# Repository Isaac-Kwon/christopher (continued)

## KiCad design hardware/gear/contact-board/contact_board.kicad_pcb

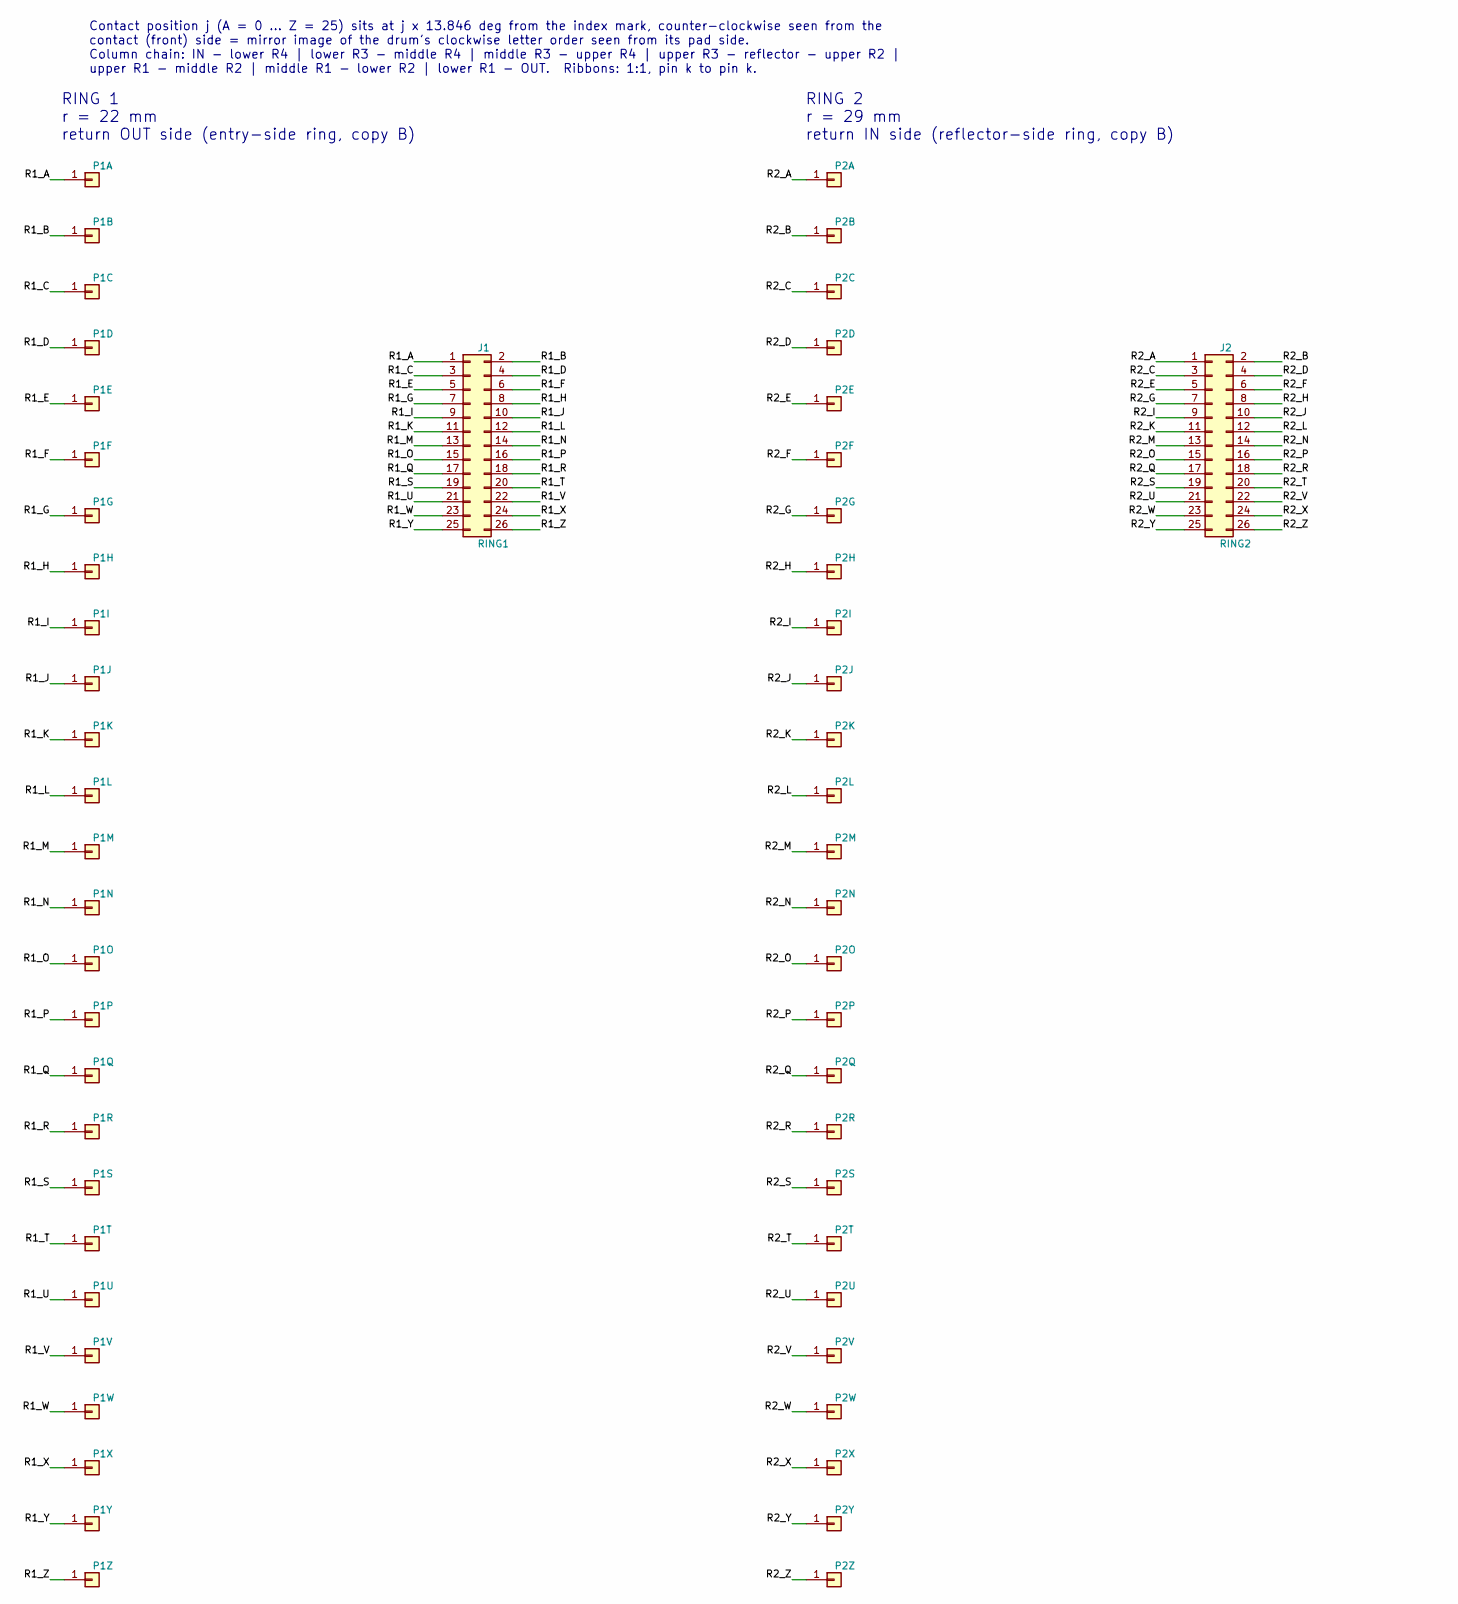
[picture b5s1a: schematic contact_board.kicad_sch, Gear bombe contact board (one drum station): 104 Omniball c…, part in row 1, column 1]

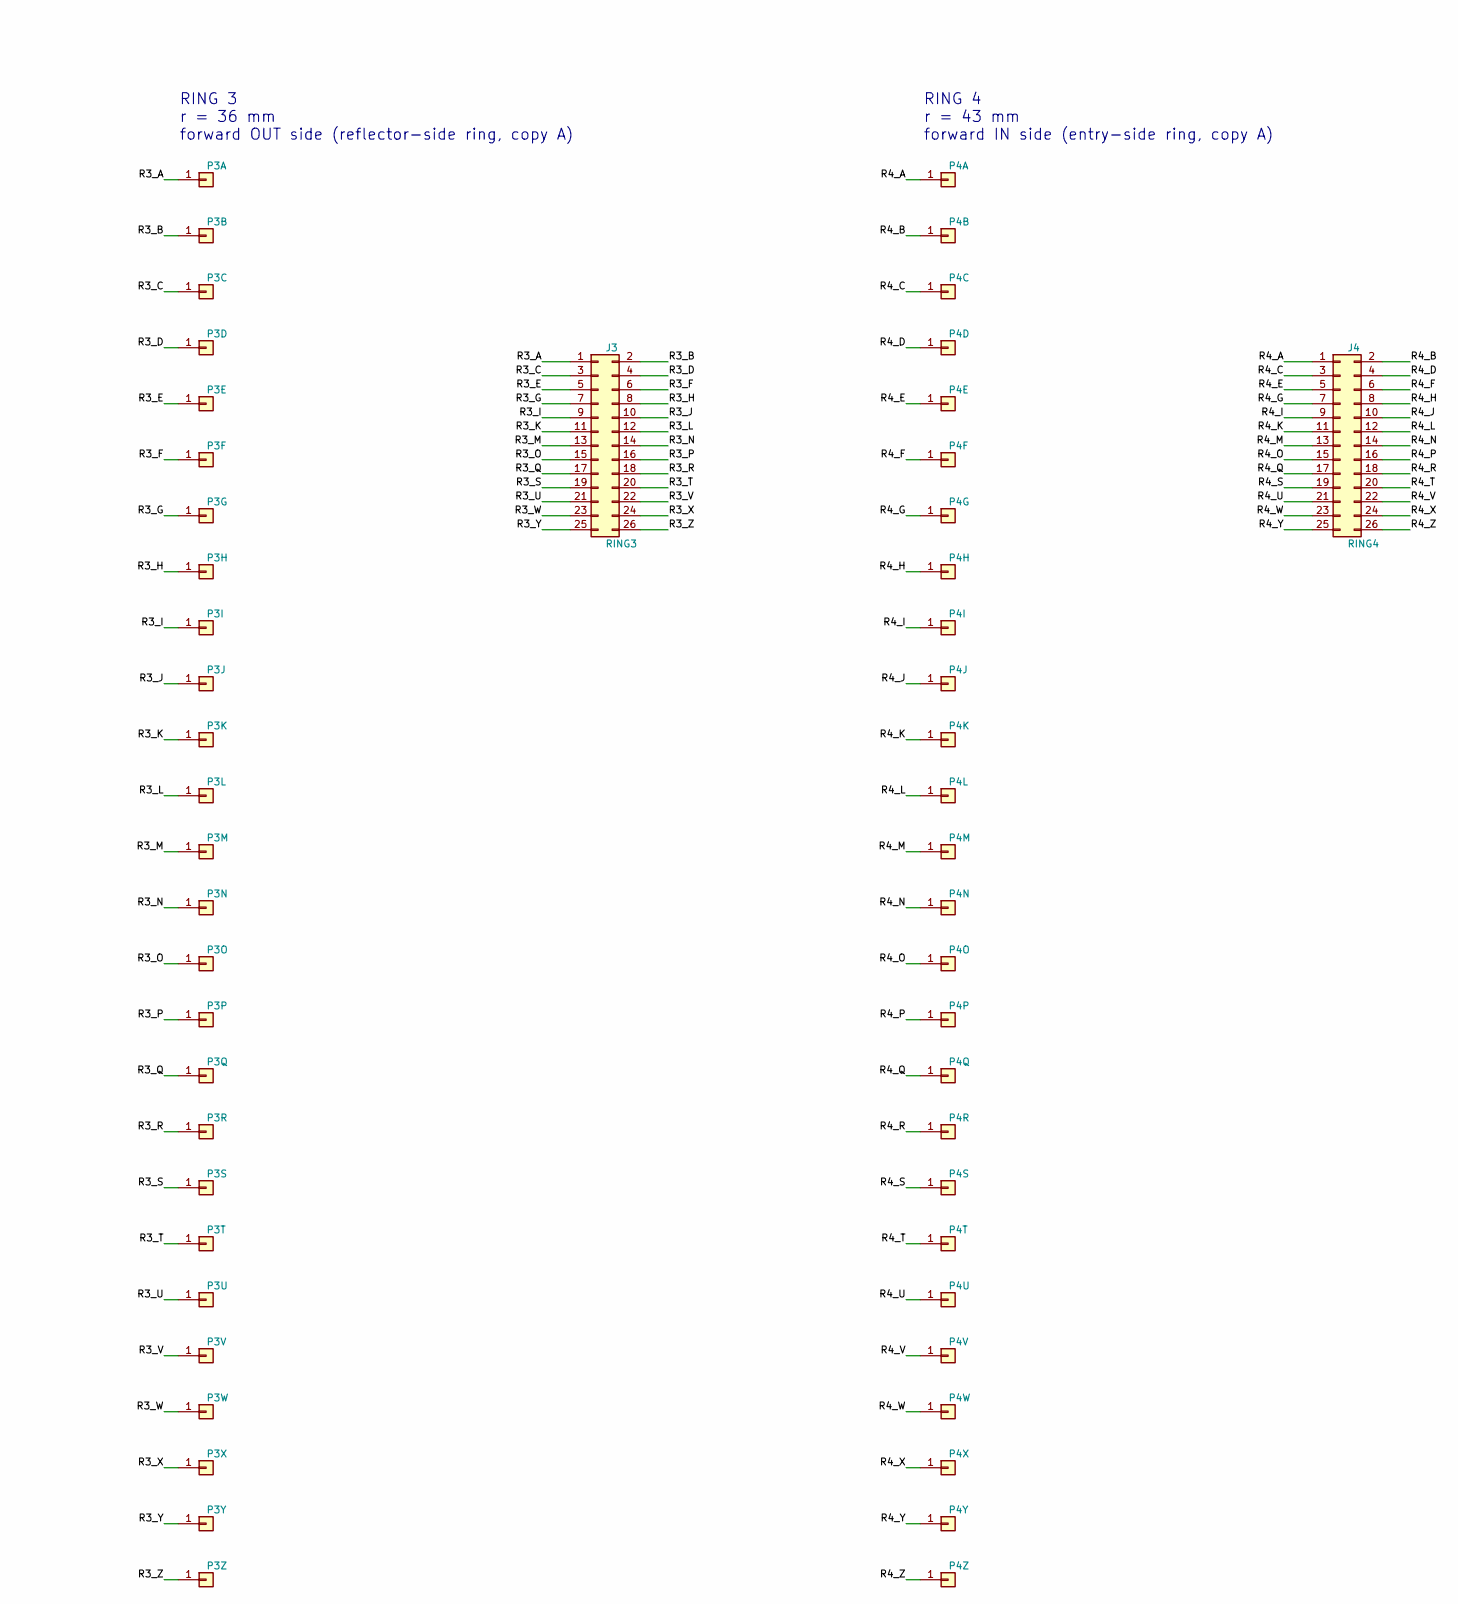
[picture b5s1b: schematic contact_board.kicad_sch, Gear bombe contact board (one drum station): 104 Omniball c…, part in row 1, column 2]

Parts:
J1: RING1; IDC-Header_2x13_P2.54mm_Vertical
J2: RING2; IDC-Header_2x13_P2.54mm_Vertical
J3: RING3; IDC-Header_2x13_P2.54mm_Vertical
J4: RING4; IDC-Header_2x13_P2.54mm_Vertical
P1A: 7845-0 R1A; Omniball_7845-0-15-20-52-14-11-0
P1B: 7845-0 R1B; Omniball_7845-0-15-20-52-14-11-0
P1C: 7845-0 R1C; Omniball_7845-0-15-20-52-14-11-0
P1D: 7845-0 R1D; Omniball_7845-0-15-20-52-14-11-0
P1E: 7845-0 R1E; Omniball_7845-0-15-20-52-14-11-0
P1F: 7845-0 R1F; Omniball_7845-0-15-20-52-14-11-0
P1G: 7845-0 R1G; Omniball_7845-0-15-20-52-14-11-0
P1H: 7845-0 R1H; Omniball_7845-0-15-20-52-14-11-0
P1I: 7845-0 R1I; Omniball_7845-0-15-20-52-14-11-0
P1J: 7845-0 R1J; Omniball_7845-0-15-20-52-14-11-0
P1K: 7845-0 R1K; Omniball_7845-0-15-20-52-14-11-0
P1L: 7845-0 R1L; Omniball_7845-0-15-20-52-14-11-0
P1M: 7845-0 R1M; Omniball_7845-0-15-20-52-14-11-0
P1N: 7845-0 R1N; Omniball_7845-0-15-20-52-14-11-0
P1O: 7845-0 R1O; Omniball_7845-0-15-20-52-14-11-0
P1P: 7845-0 R1P; Omniball_7845-0-15-20-52-14-11-0
P1Q: 7845-0 R1Q; Omniball_7845-0-15-20-52-14-11-0
P1R: 7845-0 R1R; Omniball_7845-0-15-20-52-14-11-0
P1S: 7845-0 R1S; Omniball_7845-0-15-20-52-14-11-0
P1T: 7845-0 R1T; Omniball_7845-0-15-20-52-14-11-0
P1U: 7845-0 R1U; Omniball_7845-0-15-20-52-14-11-0
P1V: 7845-0 R1V; Omniball_7845-0-15-20-52-14-11-0
P1W: 7845-0 R1W; Omniball_7845-0-15-20-52-14-11-0
P1X: 7845-0 R1X; Omniball_7845-0-15-20-52-14-11-0
P1Y: 7845-0 R1Y; Omniball_7845-0-15-20-52-14-11-0
P1Z: 7845-0 R1Z; Omniball_7845-0-15-20-52-14-11-0
P2A: 7845-0 R2A; Omniball_7845-0-15-20-52-14-11-0
P2B: 7845-0 R2B; Omniball_7845-0-15-20-52-14-11-0
P2C: 7845-0 R2C; Omniball_7845-0-15-20-52-14-11-0
P2D: 7845-0 R2D; Omniball_7845-0-15-20-52-14-11-0
P2E: 7845-0 R2E; Omniball_7845-0-15-20-52-14-11-0
P2F: 7845-0 R2F; Omniball_7845-0-15-20-52-14-11-0
P2G: 7845-0 R2G; Omniball_7845-0-15-20-52-14-11-0
P2H: 7845-0 R2H; Omniball_7845-0-15-20-52-14-11-0
P2I: 7845-0 R2I; Omniball_7845-0-15-20-52-14-11-0
P2J: 7845-0 R2J; Omniball_7845-0-15-20-52-14-11-0
P2K: 7845-0 R2K; Omniball_7845-0-15-20-52-14-11-0
P2L: 7845-0 R2L; Omniball_7845-0-15-20-52-14-11-0
P2M: 7845-0 R2M; Omniball_7845-0-15-20-52-14-11-0
P2N: 7845-0 R2N; Omniball_7845-0-15-20-52-14-11-0
P2O: 7845-0 R2O; Omniball_7845-0-15-20-52-14-11-0
P2P: 7845-0 R2P; Omniball_7845-0-15-20-52-14-11-0
P2Q: 7845-0 R2Q; Omniball_7845-0-15-20-52-14-11-0
P2R: 7845-0 R2R; Omniball_7845-0-15-20-52-14-11-0
P2S: 7845-0 R2S; Omniball_7845-0-15-20-52-14-11-0
P2T: 7845-0 R2T; Omniball_7845-0-15-20-52-14-11-0
P2U: 7845-0 R2U; Omniball_7845-0-15-20-52-14-11-0
P2V: 7845-0 R2V; Omniball_7845-0-15-20-52-14-11-0
P2W: 7845-0 R2W; Omniball_7845-0-15-20-52-14-11-0
P2X: 7845-0 R2X; Omniball_7845-0-15-20-52-14-11-0
P2Y: 7845-0 R2Y; Omniball_7845-0-15-20-52-14-11-0
P2Z: 7845-0 R2Z; Omniball_7845-0-15-20-52-14-11-0
P3A: 7845-0 R3A; Omniball_7845-0-15-20-52-14-11-0
P3B: 7845-0 R3B; Omniball_7845-0-15-20-52-14-11-0
P3C: 7845-0 R3C; Omniball_7845-0-15-20-52-14-11-0
P3D: 7845-0 R3D; Omniball_7845-0-15-20-52-14-11-0
P3E: 7845-0 R3E; Omniball_7845-0-15-20-52-14-11-0
P3F: 7845-0 R3F; Omniball_7845-0-15-20-52-14-11-0
P3G: 7845-0 R3G; Omniball_7845-0-15-20-52-14-11-0
P3H: 7845-0 R3H; Omniball_7845-0-15-20-52-14-11-0
P3I: 7845-0 R3I; Omniball_7845-0-15-20-52-14-11-0
P3J: 7845-0 R3J; Omniball_7845-0-15-20-52-14-11-0
P3K: 7845-0 R3K; Omniball_7845-0-15-20-52-14-11-0
P3L: 7845-0 R3L; Omniball_7845-0-15-20-52-14-11-0
P3M: 7845-0 R3M; Omniball_7845-0-15-20-52-14-11-0
P3N: 7845-0 R3N; Omniball_7845-0-15-20-52-14-11-0
P3O: 7845-0 R3O; Omniball_7845-0-15-20-52-14-11-0
P3P: 7845-0 R3P; Omniball_7845-0-15-20-52-14-11-0
P3Q: 7845-0 R3Q; Omniball_7845-0-15-20-52-14-11-0
P3R: 7845-0 R3R; Omniball_7845-0-15-20-52-14-11-0
P3S: 7845-0 R3S; Omniball_7845-0-15-20-52-14-11-0
P3T: 7845-0 R3T; Omniball_7845-0-15-20-52-14-11-0
P3U: 7845-0 R3U; Omniball_7845-0-15-20-52-14-11-0
P3V: 7845-0 R3V; Omniball_7845-0-15-20-52-14-11-0
P3W: 7845-0 R3W; Omniball_7845-0-15-20-52-14-11-0
P3X: 7845-0 R3X; Omniball_7845-0-15-20-52-14-11-0
P3Y: 7845-0 R3Y; Omniball_7845-0-15-20-52-14-11-0
P3Z: 7845-0 R3Z; Omniball_7845-0-15-20-52-14-11-0
P4A: 7845-0 R4A; Omniball_7845-0-15-20-52-14-11-0
P4B: 7845-0 R4B; Omniball_7845-0-15-20-52-14-11-0
P4C: 7845-0 R4C; Omniball_7845-0-15-20-52-14-11-0
P4D: 7845-0 R4D; Omniball_7845-0-15-20-52-14-11-0
P4E: 7845-0 R4E; Omniball_7845-0-15-20-52-14-11-0
P4F: 7845-0 R4F; Omniball_7845-0-15-20-52-14-11-0
P4G: 7845-0 R4G; Omniball_7845-0-15-20-52-14-11-0
P4H: 7845-0 R4H; Omniball_7845-0-15-20-52-14-11-0
P4I: 7845-0 R4I; Omniball_7845-0-15-20-52-14-11-0
P4J: 7845-0 R4J; Omniball_7845-0-15-20-52-14-11-0
P4K: 7845-0 R4K; Omniball_7845-0-15-20-52-14-11-0
P4L: 7845-0 R4L; Omniball_7845-0-15-20-52-14-11-0
P4M: 7845-0 R4M; Omniball_7845-0-15-20-52-14-11-0
P4N: 7845-0 R4N; Omniball_7845-0-15-20-52-14-11-0
P4O: 7845-0 R4O; Omniball_7845-0-15-20-52-14-11-0
P4P: 7845-0 R4P; Omniball_7845-0-15-20-52-14-11-0
P4Q: 7845-0 R4Q; Omniball_7845-0-15-20-52-14-11-0
P4R: 7845-0 R4R; Omniball_7845-0-15-20-52-14-11-0
P4S: 7845-0 R4S; Omniball_7845-0-15-20-52-14-11-0
P4T: 7845-0 R4T; Omniball_7845-0-15-20-52-14-11-0
P4U: 7845-0 R4U; Omniball_7845-0-15-20-52-14-11-0
P4V: 7845-0 R4V; Omniball_7845-0-15-20-52-14-11-0
P4W: 7845-0 R4W; Omniball_7845-0-15-20-52-14-11-0
P4X: 7845-0 R4X; Omniball_7845-0-15-20-52-14-11-0
P4Y: 7845-0 R4Y; Omniball_7845-0-15-20-52-14-11-0
P4Z: 7845-0 R4Z; Omniball_7845-0-15-20-52-14-11-0

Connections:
/R1_A: J1.1, P1A.1
/R1_B: J1.2, P1B.1
/R1_C: J1.3, P1C.1
/R1_D: J1.4, P1D.1
/R1_E: J1.5, P1E.1
/R1_F: J1.6, P1F.1
/R1_G: J1.7, P1G.1
/R1_H: J1.8, P1H.1
/R1_I: J1.9, P1I.1
/R1_J: J1.10, P1J.1
/R1_K: J1.11, P1K.1
/R1_L: J1.12, P1L.1
/R1_M: J1.13, P1M.1
/R1_N: J1.14, P1N.1
/R1_O: J1.15, P1O.1
/R1_P: J1.16, P1P.1
/R1_Q: J1.17, P1Q.1
/R1_R: J1.18, P1R.1
/R1_S: J1.19, P1S.1
/R1_T: J1.20, P1T.1
/R1_U: J1.21, P1U.1
/R1_V: J1.22, P1V.1
/R1_W: J1.23, P1W.1
/R1_X: J1.24, P1X.1
/R1_Y: J1.25, P1Y.1
/R1_Z: J1.26, P1Z.1
/R2_A: J2.1, P2A.1
/R2_B: J2.2, P2B.1
/R2_C: J2.3, P2C.1
/R2_D: J2.4, P2D.1
/R2_E: J2.5, P2E.1
/R2_F: J2.6, P2F.1
/R2_G: J2.7, P2G.1
/R2_H: J2.8, P2H.1
/R2_I: J2.9, P2I.1
/R2_J: J2.10, P2J.1
/R2_K: J2.11, P2K.1
/R2_L: J2.12, P2L.1
/R2_M: J2.13, P2M.1
/R2_N: J2.14, P2N.1
/R2_O: J2.15, P2O.1
/R2_P: J2.16, P2P.1
/R2_Q: J2.17, P2Q.1
/R2_R: J2.18, P2R.1
/R2_S: J2.19, P2S.1
/R2_T: J2.20, P2T.1
/R2_U: J2.21, P2U.1
/R2_V: J2.22, P2V.1
/R2_W: J2.23, P2W.1
/R2_X: J2.24, P2X.1
/R2_Y: J2.25, P2Y.1
/R2_Z: J2.26, P2Z.1
/R3_A: J3.1, P3A.1
/R3_B: J3.2, P3B.1
/R3_C: J3.3, P3C.1
/R3_D: J3.4, P3D.1
/R3_E: J3.5, P3E.1
/R3_F: J3.6, P3F.1
/R3_G: J3.7, P3G.1
/R3_H: J3.8, P3H.1
/R3_I: J3.9, P3I.1
/R3_J: J3.10, P3J.1
/R3_K: J3.11, P3K.1
/R3_L: J3.12, P3L.1
/R3_M: J3.13, P3M.1
/R3_N: J3.14, P3N.1
/R3_O: J3.15, P3O.1
/R3_P: J3.16, P3P.1
/R3_Q: J3.17, P3Q.1
/R3_R: J3.18, P3R.1
/R3_S: J3.19, P3S.1
/R3_T: J3.20, P3T.1
/R3_U: J3.21, P3U.1
/R3_V: J3.22, P3V.1
/R3_W: J3.23, P3W.1
/R3_X: J3.24, P3X.1
/R3_Y: J3.25, P3Y.1
/R3_Z: J3.26, P3Z.1
/R4_A: J4.1, P4A.1
/R4_B: J4.2, P4B.1
/R4_C: J4.3, P4C.1
/R4_D: J4.4, P4D.1
/R4_E: J4.5, P4E.1
/R4_F: J4.6, P4F.1
/R4_G: J4.7, P4G.1
/R4_H: J4.8, P4H.1
/R4_I: J4.9, P4I.1
/R4_J: J4.10, P4J.1
/R4_K: J4.11, P4K.1
/R4_L: J4.12, P4L.1
/R4_M: J4.13, P4M.1
/R4_N: J4.14, P4N.1
/R4_O: J4.15, P4O.1
/R4_P: J4.16, P4P.1
/R4_Q: J4.17, P4Q.1
/R4_R: J4.18, P4R.1
/R4_S: J4.19, P4S.1
/R4_T: J4.20, P4T.1
/R4_U: J4.21, P4U.1
/R4_V: J4.22, P4V.1
/R4_W: J4.23, P4W.1
/R4_X: J4.24, P4X.1
/R4_Y: J4.25, P4Y.1
/R4_Z: J4.26, P4Z.1

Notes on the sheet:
RING 1 r = 22 mm return OUT side (entry-side ring, copy B)
RING 2 r = 29 mm return IN side (reflector-side ring, copy B)
RING 3 r = 36 mm forward OUT side (reflector-side ring, copy A)
RING 4 r = 43 mm forward IN side (entry-side ring, copy A)
Contact position j (A = 0 ... Z = 25) sits at j x 13.846 deg from the index mark, counter-clockwise seen from the contact (front) side = mirror image of the drum's clockwise letter order seen from its pad side. Column chain: IN - lower R4 | lower R3 - middle R4 | middle R3 - upper R4 | upper R3 - r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

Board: 4 copper layers, 112 parts (4 on the bottom side), 104 nets, no tracks yet.

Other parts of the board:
H1, H4: NPTH 3.2; NPTH_3.2mm
H2, H3: NPTH 3; NPTH_3mm

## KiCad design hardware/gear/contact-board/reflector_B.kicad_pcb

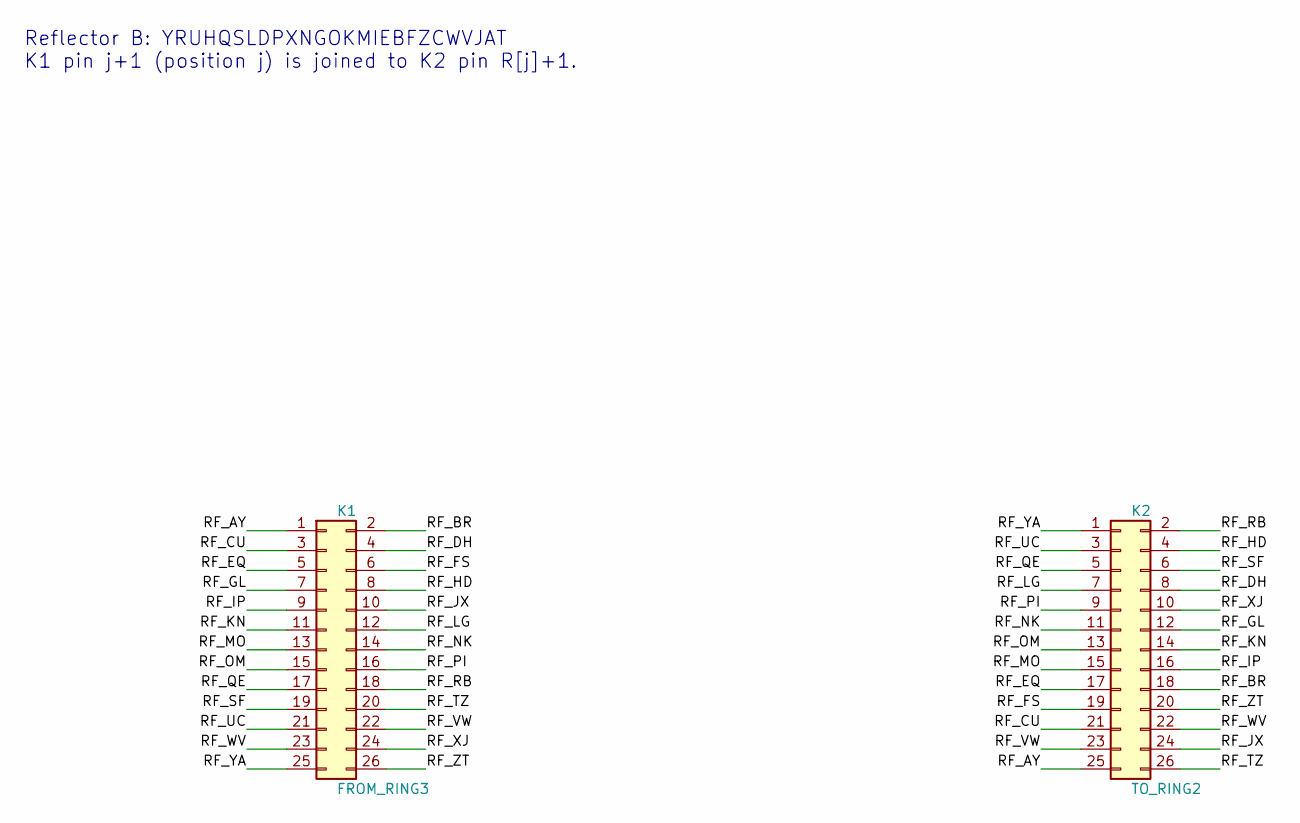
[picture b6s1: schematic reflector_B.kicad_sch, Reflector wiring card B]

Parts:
K1: FROM_RING3; IDC-Header_2x13_P2.54mm_Vertical
K2: TO_RING2; IDC-Header_2x13_P2.54mm_Vertical

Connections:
/RF_AY: K1.1, K2.25
/RF_BR: K1.2, K2.18
/RF_CU: K1.3, K2.21
/RF_DH: K1.4, K2.8
/RF_EQ: K1.5, K2.17
/RF_FS: K1.6, K2.19
/RF_GL: K1.7, K2.12
/RF_HD: K1.8, K2.4
/RF_IP: K1.9, K2.16
/RF_JX: K1.10, K2.24
/RF_KN: K1.11, K2.14
/RF_LG: K1.12, K2.7
/RF_MO: K1.13, K2.15
/RF_NK: K1.14, K2.11
/RF_OM: K1.15, K2.13
/RF_PI: K1.16, K2.9
/RF_QE: K1.17, K2.5
/RF_RB: K1.18, K2.2
/RF_SF: K1.19, K2.6
/RF_TZ: K1.20, K2.26
/RF_UC: K1.21, K2.3
/RF_VW: K1.22, K2.23
/RF_WV: K1.23, K2.22
/RF_XJ: K1.24, K2.10
/RF_YA: K1.25, K2.1
/RF_ZT: K1.26, K2.20

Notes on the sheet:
Reflector B: YRUHQSLDPXNGOKMIEBFZCWVJAT K1 pin j+1 (position j) is joined to K2 pin R[j]+1.

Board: 4 copper layers, 6 parts (2 on the bottom side), 26 nets, no tracks yet.

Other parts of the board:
H1, H2, H3, H4: NPTH 3.2; NPTH_3.2mm

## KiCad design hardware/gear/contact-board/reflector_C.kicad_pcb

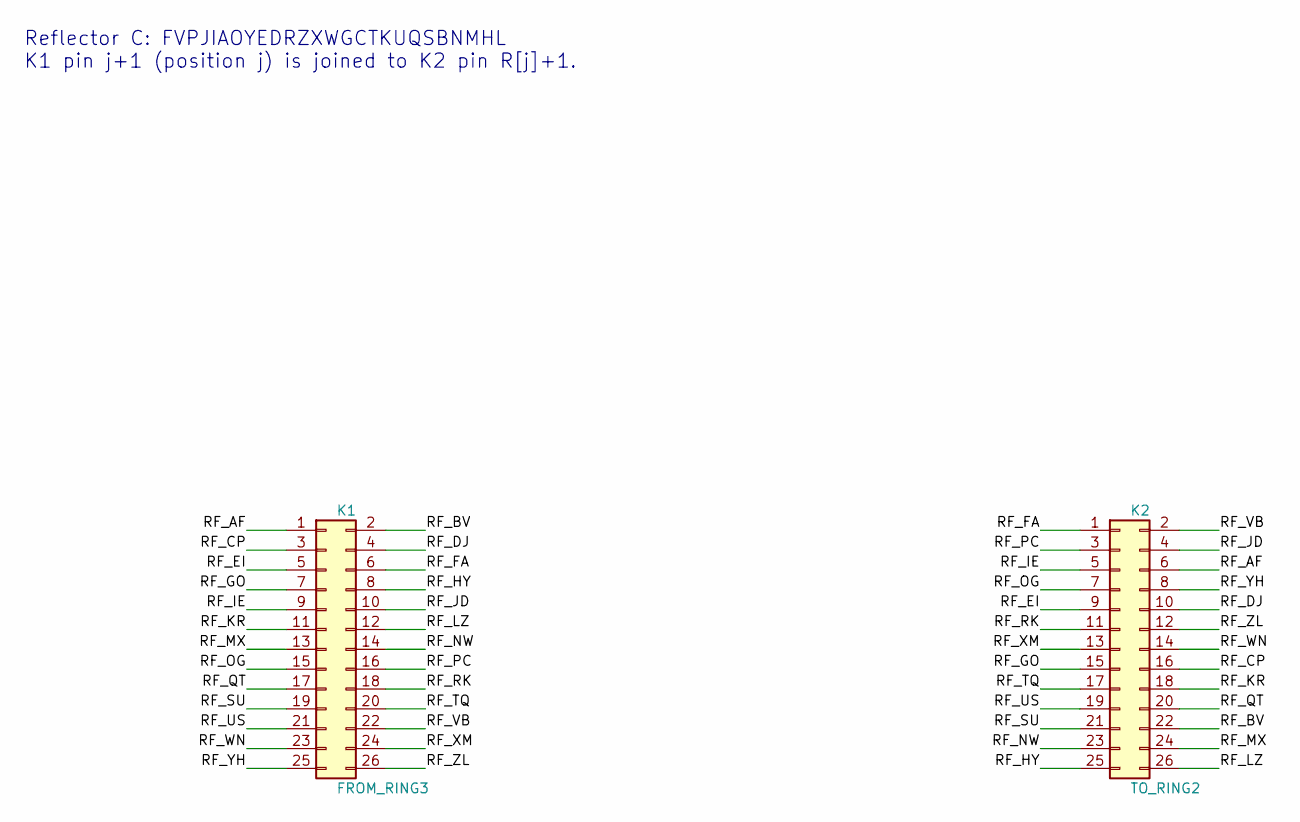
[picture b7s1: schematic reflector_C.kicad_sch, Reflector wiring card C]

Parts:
K1: FROM_RING3; IDC-Header_2x13_P2.54mm_Vertical
K2: TO_RING2; IDC-Header_2x13_P2.54mm_Vertical

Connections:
/RF_AF: K1.1, K2.6
/RF_BV: K1.2, K2.22
/RF_CP: K1.3, K2.16
/RF_DJ: K1.4, K2.10
/RF_EI: K1.5, K2.9
/RF_FA: K1.6, K2.1
/RF_GO: K1.7, K2.15
/RF_HY: K1.8, K2.25
/RF_IE: K1.9, K2.5
/RF_JD: K1.10, K2.4
/RF_KR: K1.11, K2.18
/RF_LZ: K1.12, K2.26
/RF_MX: K1.13, K2.24
/RF_NW: K1.14, K2.23
/RF_OG: K1.15, K2.7
/RF_PC: K1.16, K2.3
/RF_QT: K1.17, K2.20
/RF_RK: K1.18, K2.11
/RF_SU: K1.19, K2.21
/RF_TQ: K1.20, K2.17
/RF_US: K1.21, K2.19
/RF_VB: K1.22, K2.2
/RF_WN: K1.23, K2.14
/RF_XM: K1.24, K2.13
/RF_YH: K1.25, K2.8
/RF_ZL: K1.26, K2.12

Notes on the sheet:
Reflector C: FVPJIAOYEDRZXWGCTKUQSBNMHL K1 pin j+1 (position j) is joined to K2 pin R[j]+1.

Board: 4 copper layers, 6 parts (2 on the bottom side), 26 nets, no tracks yet.

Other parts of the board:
H1, H2, H3, H4: NPTH 3.2; NPTH_3.2mm

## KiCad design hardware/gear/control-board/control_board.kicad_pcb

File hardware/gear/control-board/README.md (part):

# 기어식 제어 보드 (구동부의 제어 보드, 회로도 · 시뮬레이션 · 기판 배치)

작성일: 2026-11-15 · 상태: **회로도(KiCad 10) 생성·ERC 0건, 넷리스트 구조 검사 335항목, 하드웨어·기구·펌웨어·릴레이 레지스터 연동 시뮬레이션, 음성 시험 19종, 기판 배치(미배선) 생성·검증 완료. 배선은 사용자가.** 같은 날 슬롯 원판의 각도(L4 여유)와 위치 원판의 모델(CAD와 일치)을 고치고, `HOME` 끝의 `CLEAR`(결정 0003 4.4절 (나))를 더함 · 관련: `docs/decisions/0003-interfaces.md`(4.2–4.6절, 5.2절, 6·7절), `docs/decisions/0001-test-register-timing.md`, `docs/decisions/0002-gear-detail-decisions.md` 5·10·11절, `hardware/gear/layout.md` 3.7·3.8절, `hardware/common/power-unit.md`, `hardware/common/unit-tester/README.md`(같은 부품 계열)

**표기.** **(계산)** = 이 문서의 산술, **(추정)** = 실측 전 값, **(미확인)** = 데이터시트로 확인하지 못한 것.

## 1. 무엇인가, 원칙

기어식 뱅크의 구동부에 들어가는 보드다. `docs/PLAN.md` 0절 7a의 미설계 항목이었다. 하는 일은 둘뿐이다.

1. **타이밍 신호 조건화**: 슬롯 원판의 광센서 셋 → `STROBE`·`JUDGE`·`CLEAR`를 24 V 레벨(결정 0003 2.2절)로 제어 커넥터에 낸다. 이 경로에는 **펌웨어가 없다**(센서 → RC → 74HC14 → 74HC 게이트 → TBD62783A → 자동 복귀 퓨즈 → 핀). 정지를 정하는 것은 테스트 레지스터의 릴레이다. 이 보드는 "언제"만 알린다.
2. **구동 제어**: 폐루프 스테퍼 구동기에 enable / step / dir를 주고(결정 0002 5절), 정지 자리로의 되돌림 · 재출발 · HOME · END · `POS` · 48 V 복귀 규칙을 맡는다. 마이크로컨트롤러는 **Raspberry Pi Pico**(단위 시험기와 같은 모듈)다. 전자 장치가 하는 일은 구동 제어와 신호 조건화에 한정되고 판정에는 관여하지 않는다(`design-brief.md` 1절).

구동기를 step / dir / enable로 고른 이유: 폐루프 스테퍼(예: Leadshine CS-M23485 계열)에는 자체 가감속 프로파일이 없다. 10,400 pps에서 정지 상태로부터 바로 스텝을 주면 탈조하므로 가감속 램프를 Pico가 만든다. "run / stop" 방식의 구동기는 속도 지령이 아날로그 또는 내부 프로그램이어서 되돌림(역회전, 위치 이동)을 못 한다. 구동기는 2,600 pulse/rev로 설정한다: 4:1 벨트에서 모터 한 바퀴 = 빠른 축 1/4 바퀴, 한 위치 = 13.846° (계산) = 모터 55.38° = **400 스텝**, 60 rpm = 26 위치/초 = **10,400 pps** (계산).

### 1.1 타이밍 경로 (하드웨어, 결정 0003 L1–L9)

```
광센서 3 (STROBE 트랙 · JUDGE 트랙 · CLEAR 트랙)
  → 4.7k 풀업(3.3 V) → 1k + 4.7n (약 5 µs) → 74HC14 → SLOT_S / SLOT_J / SLOT_C (하이 = 슬롯)
  STROBE_G = SLOT_S & TXE
  CLEAR_G  = SLOT_C & TXE
  JUDGE_G  = SLOT_J & SEEN & TXE
  TXE  = TXEN | CYC                      TXEN = Pico가 줌(HOME · 되돌림 중 0)
  CYC  : STROBE_G가 높은 동안 세트, CLEAR_G의 내림에서 클리어   (L7: 시작한 주기는 끝낸다)
         전원 투입 | HOMING에서 리셋 (74HC02의 남던 게이트: CYC_R_N = NOR(POR | HOMING))
  SEEN : STROBE_G의 오름에서 세트, 전원 투입 | HOMING | STOP_LATCH의 내림(RC 펄스)에서 클리어   (L8)
  → TBD62783A 채널(+24V_SW) → 자동 복귀 퓨즈(유지 30 mA 이상, 트립 100 mA 이하) → J_CTRL 핀 1 / 34 / 35
```

- 슬롯 각도(커넥터 면)는 `layout.md` 3.8절의 값이고, 원본은 CAD의 `hardware/gear/cad/params.py`(`SLOT_STEPS`, 한 위치 400스텝)다. 펌웨어 모델과 시뮬레이션이 그 파일을 읽는다: `STROBE` −26…+47스텝 = −2.50…+4.52 ms(보정 뒤 대표), `JUDGE` +89…+173 = +8.56…+16.63, `CLEAR` +194…+330 = +18.65…+31.73 (`STROBE` 접점 시작 기준, 패드 가운데는 +31.2스텝 = +3 ms, 60 rpm). 결정 0003 L2–L5에 각각 0.5 ms 이상의 공차 여유를 남긴 값이다(L2는 보정한 쪽의 식, 6절 1번). 보드는 **시간을 만들지 않는다**: 슬롯이 폭과 간격을 정한다. 폭 · 간격의 하한(L1–L6)은 속도가 60 rpm 이하이면 모든 구간이 시간으로 길어지므로 저속 · 가속 구간에서도 성립한다. 가감속 램프는 속도가 60 rpm을 넘지 않게 되어 있다.
- **L8을 STOP_LATCH의 내림 "에지"로** 지운다(레벨이 아님). 레벨로 하면 정지 판정(`JUDGE`) 도중 `STOP_LATCH`가 오를 때 `JUDGE`가 잘려 정지 릴레이가 자기 유지에 들기 전에 j가 열린다. 에지는 해제 때에만 지운다. 에지 펄스는 SL_N(= ¬STOP_LATCH)과 그 RC 지연(R61 47k · C51 10n, 약 0.5 ms)의 AND다.
- **CYC**가 필요한 이유: L7은 "`STROBE`를 낸 위치에는 `JUDGE`와 `CLEAR`를 반드시 낸다"이다. 펌웨어가 `TXEN`을 주기 한가운데서 내려도(되돌림) 시작한 주기는 끝난다.
- **CYC를 `HOMING`이 리셋하는 이유**(2026-11-15): `HOME`은 서 있을 때만 시작하고, 조작 정지와 정지 뒤 되돌림은 주기 사이에 서므로 그때 `CYC`는 이미 0이다. `CYC`가 남는 것은 비상 정지가 주기를 끊었을 때뿐이다(로직은 `+24V_L`이라 남는다). 그대로 두면 `+24V_SW`가 돌아올 때 슬롯 안에 서 있으면 그 출력이 나오고, `HOME`이 거꾸로 움직이면 그 칸의 `STROBE` 슬롯에서 `STROBE`가 나가며(0003 4.4 ① 위반), 앞으로 움직이면 `CLEAR`가 하나 더 나간다. 그래서 펌웨어는 비상 정지 때부터 `HOME`이 끝날 때까지 `HOMING`을 세워 두고(`SEEN`과 `CYC`를 지운 채), 끊긴 주기의 `CLEAR`는 `HOME` 끝의 `CLEAR`(1.2절)가 대신한다. 새 부품은 없다(74HC02의 남던 게이트 하나).
- **`HOME` 끝의 `CLEAR`**(결정 0003 4.4절 (나)): `CLEAR_G`는 `SEEN`을 보지 않으므로(`SLOT_C & TXE`), 펌웨어가 `HOMING`을 세운 채 `CLEAR` 슬롯 하나 동안만 `TXEN`을 올리면 `JUDGE` 없이 `CLEAR` 한 번이 나간다. 방법은 1.2절 표의 HOME.
- 슬롯 센서는 `+24V_SW`가 아니라 `+24V_L`에서 먹이고 출력단(TBD62783A U60)만 `+24V_SW`에서 먹인다(`power-unit.md` 2.2절). 비상 정지(`K_E`)가 `+24V_SW`를 끊으면 타이밍 출력과 PUL / DIR / ENA가 함께 사라진다.
- **보정**: STROBE 보정은 결정대로 센서 브래킷의 회전이며 이 보드에는 전자적 보정이 없다. 오실로스코프용으로 조건화한 슬롯 신호 `SLOT_S / SLOT_J / SLOT_C`와 0 V를 4핀 헤더 `J7`에 낸다(커넥터 면 신호는 `J_CTRL` 핀 1 / 34 / 35).

### 1.2 구동 제어 (펌웨어 모델 `firmware_model.py`)

실행 가능한 명세다(MicroPython으로 옮길 때의 기준). 상태: `REST · RUN · STOPDEC · CREEPOUT · RET · HBACK · HSEARCH · HDEC · HGO · HMOVE · HFLUSH`.

| 항목 | 동작 |
|---|---|
| 램프 | 가속 8×10⁵ steps/s², 정지 감속 1.2×10⁶ steps/s² (모터 축 약 1.1 / 1.3 N·m, 사다리꼴, **(추정)** G.2에서 확정). 속도는 10,400 pps를 넘지 않는다 |
| 48 V 복귀 규칙 (`power-unit.md` 4.2절) | `RUNARM`: `V48_OK`(KM3의 a 보조 접점, 24 V 레벨) 또는 `SW_OK`가 꺼지면 해제, `V48_OK` ∧ `SW_OK` ∧ `RUN` = 0이면 세트. 전진은 `RUN` ∧ `RUNARM`일 때만 |
| 정지 (`STOP_LATCH`의 오름) | 감속 → 앞으로 기어서 그 주기의 `CLEAR`가 끝나는 곳을 잡는다(`s_clear_end`) → 그 지점 +10 스텝(정지 자리 `CLEAR` 끝 +330 … 다음 `STROBE` 시작 +374 안, 44 스텝 = 1.32°, 최악 약 20스텝: 6절 3번)으로 이동. 뒤로 가야 하면 `TXEN` = 0. 서면 `STOPPED` = 1, `POS` = 정지 위치의 (l, m, r) |
| 재출발 | `RUN` 오름(해제 버튼) + `RUNARM` → 전진, 첫 `STROBE`는 n + 1. 위치 n은 다시 시험하지 않는다 |
| 조작 정지 (`RUN`만 내려감) | 감속 → 슬롯 밖이고 주기가 끝난 곳까지 기어서 선다(레지스터에 반쯤 끝난 주기가 남지 않게) |
| HOME (`HOME` 100 ms 이상, `RUN` = `STOP_LATCH` = 0) | `HOMING` = 1, `TXEN` = 0. 계수기가 맞으면 짧은 쪽 방향으로 위치 이동(최대 8,788 위치), 맞지 않으면 앞으로 탐색(최대 17,576 위치, 속도는 `RUN`의 2배. 주기 축의 0번째 회전 안(`I_M` ∧ `I_S`)에서 시작하면 먼저 그 밖으로 물러남) → 세 인덱스 센서가 모두 높은 동안 `STROBE` 슬롯이 오르는 곳을 원점 표시로 삼는다. **마지막 접근(`HFLUSH`, `HOME` 끝의 `CLEAR`)**: 위치 이동 · 탐색은 원위치(칸의 −70)가 아니라 그보다 슬롯 있는 칸 하나 앞, 곧 이전 회전의 k = 25 칸의 같은 자리(원위치 − 2,000 스텝)로 간다. 거기서 `HOMING` = 1, `TXEN` = 0인 채 3,000 pps(60 rpm 이하)로 앞으로 2,000 스텝을 가며, 그 칸의 `JUDGE` 슬롯이 끝나는 에지에서 `TXEN` = 1, `CLEAR` 슬롯이 끝나는 에지에서 `TXEN` = 0으로 한다 → `CLEAR` 한 번(136 스텝 = 45 ms ≥ 12.5), `STROBE` 슬롯은 `TXEN` = 0일 때 지나고 `JUDGE`는 `SEEN`이 막는다. 원위치에 서면 세 인덱스를 확인하고 `AT_HOME` = 1 (`CLEAR`가 끝난 뒤 약 0.5 s, 다음 `STROBE`는 그 뒤). 슬롯 에지를 못 보았으면 한 칸 물러나 다시 지나간다 |
| `END` | 마지막 위치(시험 순서 n = 26 Q + k로 기본 17,575, 또는 676위치 구간의 끝 675)의 `CLEAR`가 끝나면 감속 · 정지 → `END` = `STOPPED` = 1. 이후 `RUN` 무시, `HOME`이 푼다(`HOME` 끝의 `CLEAR`는 n = 17,575 칸을 지나지만 `HOMING` 중이라 `END`로 세지 않는다) |
| 비상 정지 · 덮개 | `SW_OK`가 꺼지면 구동기 enable 해제, 펌웨어는 운동을 잊고 **HOME을 요구**(주기가 어디서 끊겼는지 모르므로)하며, **`HOME`이 끝날 때까지 `HOMING` = 1**로 둔다(`SEEN` · `CYC`를 지워 끊긴 주기의 나머지가 `+24V_SW` 복귀 때나 `HOME` 중에 나오지 않게, 1.1절). 구동이 끊긴 뒤 축은 마찰로 미끄러져 서는데(정격 속도에서 약 180 스텝) 그 스텝은 세지 못하므로, `HOME`의 이동은 T_L 경계를 지날 때마다 남은 거리를 다시 맞춘다(한 칸 미만의 보정만 받음). 덮개(48 V만 꺼짐)는 HOME을 요구하지 않지만 `RUN`이 한 번 내려갔다 올라와야 한다 |

위치 센서(`layout.md` 3.8절 "위치 원판과 센서", CAD의 `posdisc_F/M/S`): F · M · S 축의 위치 원판마다 **T 센서**(26 슬롯, 그 축이 한 칸 갈 때 한 펄스)와 **I 센서**(그 축의 값이 0인 구간에서 높음). 펌웨어가 T 에지를 센다(전진: 오름 +1, 후진: 내림 −1, `I`가 높으면 건너뜀), `I` 오름에서 0으로 맞춘다 → l (F, 빠른 드럼), m (M), r (S). `POS0–4` = l, `POS5–9` = m, `POS10–14` = r. 후진 방향은 보드가 낸 `DIR`로 안다(손 크랭크로 거꾸로 돌리면 다음 `I`까지 틀릴 수 있다. 표시 · 대조 전용이므로 판정에 영향이 없다). `AT_HOME` = `I_L` ∧ `I_M` ∧ `I_S`이고 HOME이 끝난 자리에서만 켠다.

기구의 모델(CAD와 같음): 한 칸 = 400 스텝(주기 축 12°, 0.03°/스텝), 주기 축 한 바퀴 = 30칸 중 26칸(k = 0 … 25)에 슬롯 · 4칸(k = 26 … 29)은 자리올림 구간. **F의 원판은 빠른 드럼과 함께 연속으로 돌므로**(26:30) T_L은 빈 칸을 포함해 주기 축 한 바퀴에 30번 오고, 시험하는 칸 (Q, k)의 빠른 드럼은 l = (30 Q + k) mod 26 = (4 m + k) mod 26이다(주기마다 시작 글자가 4칸 밀림, `concept.md` 5.2절). m은 자리올림 1(주기 축 330° = 27.5칸)에서, r은 m이 25 → 0으로 갈 때 올라간다. M의 T 에지가 주기 축의 위상 표시를 겸하므로 펌웨어는 칸 번호 k를 T_M에서 27로 맞추고 T_L마다 하나씩 센다(HOME의 위치 계산에 씀). **시험 순서 n = 26 Q + k**(Q = m + 26 r)가 정지 · `END`의 순서이고, `POS`는 (l, m, r)이다. 전체 한 바퀴 = 676 주기 축 회전 = 8,112,000 스텝. T_L 경계는 `STROBE` 접점 시작 +280 스텝(`CLEAR` 오름 +194 뒤, 다음 `STROBE` 오름 1 ms 전 +364 앞)에 두어 `POS`가 "`STROBE` 오름 1 ms 전부터 `CLEAR` 오름까지" 변하지 않는다(결정 0003 4.5절). 서 있는 동안은 정지 위치를 보인다(경계가 정지 자리보다 앞이므로 펌웨어가 `CLEAR` 오름에서 잡은 값을 붙든다). 원점 표시가 세 인덱스만이 아닌 이유: 0번째 회전 안에서 빠른 드럼이 글자 0인 칸이 k = 0과 빈 칸 k = 26 둘이다. 슬롯은 k = 0에만 있으므로 "세 인덱스가 높은 동안 `STROBE` 슬롯의 오름"이 하나로 정해진다.

## 2. 회로도 구조

`gen_control.py`(표준 라이브러리만, KiCad 표준 심볼 · 풋프린트)가 만든다. 시트는 7장, 모든 넷 이름은 전역 레이블이다.

| 시트 | 내용 |
|---|---|
| `power` | `+24V_L` · `+24V_SW` 입력 단자 각각: 단자 → PTC → 직렬 P채널 MOSFET → TVS 33 V + 100 µF (결정 0003 7.3절). TSR 1-2450(24 → 5 V) → 쇼트키 → Pico `VSYS`. 센서 전원 PTC. `CHASSIS`: 장착 구멍 4 + 1 MΩ ∥ 10 nF |
| `mcu` | Pico, 리셋 단추, 부팅 중 기본값(`TXEN` 풀다운, `HOMING` · `OE` 풀업) |
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
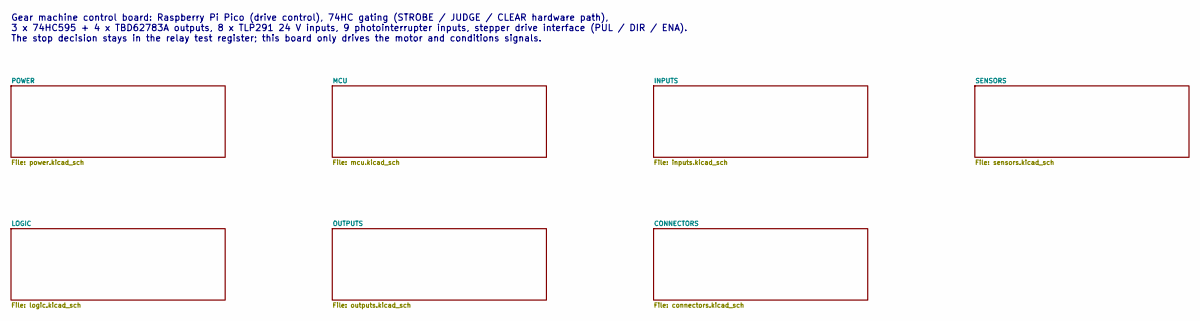
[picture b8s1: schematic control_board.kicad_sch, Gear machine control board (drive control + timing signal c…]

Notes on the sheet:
Gear machine control board: Raspberry Pi Pico (drive control), 74HC gating (STROBE / JUDGE / CLEAR hardware path), 3 x 74HC595 + 4 x TBD62783A outputs, 8 x TLP291 24 V inputs, 9 photointerrupter inputs, stepper drive interface (PUL / DIR / ENA). The stop decision stays in the relay test register; t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
